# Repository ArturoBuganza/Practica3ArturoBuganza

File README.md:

# Practica3ArturoBuganza
This is the third practice form the microcontoller laboratory

## Objectives

Build the minimum system from the designs that thei student made on the practices 1 and 2.

## Introduction

Microcontrollers are all around  he world. Each day, Microcontrollers, are more present in the many aspects of our lives: in our work, inside our houses, and in more. We can find them controlling small devices like cellphones, microwaves, washing machines, and televisions.

A microcontroller is one device or chip that is used to govern one or more processes. For example, the controller that regulates the room temperature of an air conditioner; it has a sensor that continuously measures the internal temperature and, when the preset limits are exceeded, it generates the necessary signals to adjust the temperature.

## State of the Art

### The practices and the PIC microcontroller

The main objective of this practices is to provide students the foundation to fully understand the operation of the PIC18F45K50 microcontroller. This will be achieved through 11 documents that will guide the reader to create their own electronic card or Printed Circuit Board (PCB) and to be able to program it; in order to, execute different functions.

The advantages of ta PIC microcontroller to others on the market, which is why it will be used throughout this manual, are as follows:

- Easy to operate.
- There is enough documentation to work with it and it’s easy to obtain it.
- The price is comparatively lower than its competitors.
- It has a high operating speed.
- Development tools are cheap and easy to use.
- There are a variety of hardware that can record, erase and check the behavior of PIC.
- Once you learn to handle a PIC, it will easier to handle any other models of microcontrollers.

### KiCad EDA Software

KiCad is an open source software suite for Electronic Design Automation (EDA). The programs handle Schematic Capture,
and PCB Layout with Gerber output. The suite runs on Windows, Linux and macOS and is licensed under GNU GPL v3. The
first release date was in 1992 by its original author, Jean-Pierre Charras, but is now currently under development by
the KiCad Developers Team. 

## Results

This practice is pretty fast, but it makes us look at the final product as a simulation, in order for we to obtain this we needed to export the files to make them ready to be printed or hand crafted into the silicon plate. The results were satisfiying, the screenshots are forward ahead in the Demonstration section.

### Follow the next 'Project Configuration' Steps

1. Now that your PCB is completed, you can generate the Gerber files for each layer of your board. Click on Perform design rules check as shown in Fig. 1. Then click on the Run DCR, if everything goes right you will get no message of error, as show in figure 2.

2. Click on File→Plot... Select ‘Gerber’ as ‘Plot Format,’also you must choose a folder to save your generated files. Make sure that only the next options are selected: B.Cu from ‘Layers’ box, Exclude PCB edge layer from other layers from ‘Options’ box, and Use proper filename extensions from ‘Gerber Options’ box; as shown in Fig. 3.

3. Finally, click on ‘Plot’ and then click on Generate Drill File. A new window will appear with some options on default. In the section Excellon Drill File Options select the ‘PTH and NPTH holes in single file’ box, then click on the button ‘Generate Drill File.’ Next, in the section Drill Map File Format change to ‘PDF’ box and click on ‘Generate Drill File’ again, see Fig. 4.

4. Once the Gerber and Drill files are generated, you can check your track design [here](https://www.pcbgogo.com/GerberViewer.html). Use the file with the .gbl and .drl extension.

### Report
For this practice, modify only the Conclusion section. Commit an push the changes on the fork of this repository and add
upload the link on Canvas.

### File uploads
Commit and push the files with extensions .pro, .gbl, and .drl  created once you completed all the steps of the document in the repository.

### Demonstration
Screenshot drill.

Screenshot gerber.

## Conclusion

This third practice was significantly faster than the last two. This last step allows us to look at the holes needed to drill, and the cupper pats that need to be added in the piece in order for it to work properly.

The gerber view allows us to see the paths and conections, while the drill view helps us with the holes proyection. Combining these two we get a good idea of the possible final product.

The hardest part here was to follow the steps correctly, but it wasnt that hard since it is described in the practice click by click.

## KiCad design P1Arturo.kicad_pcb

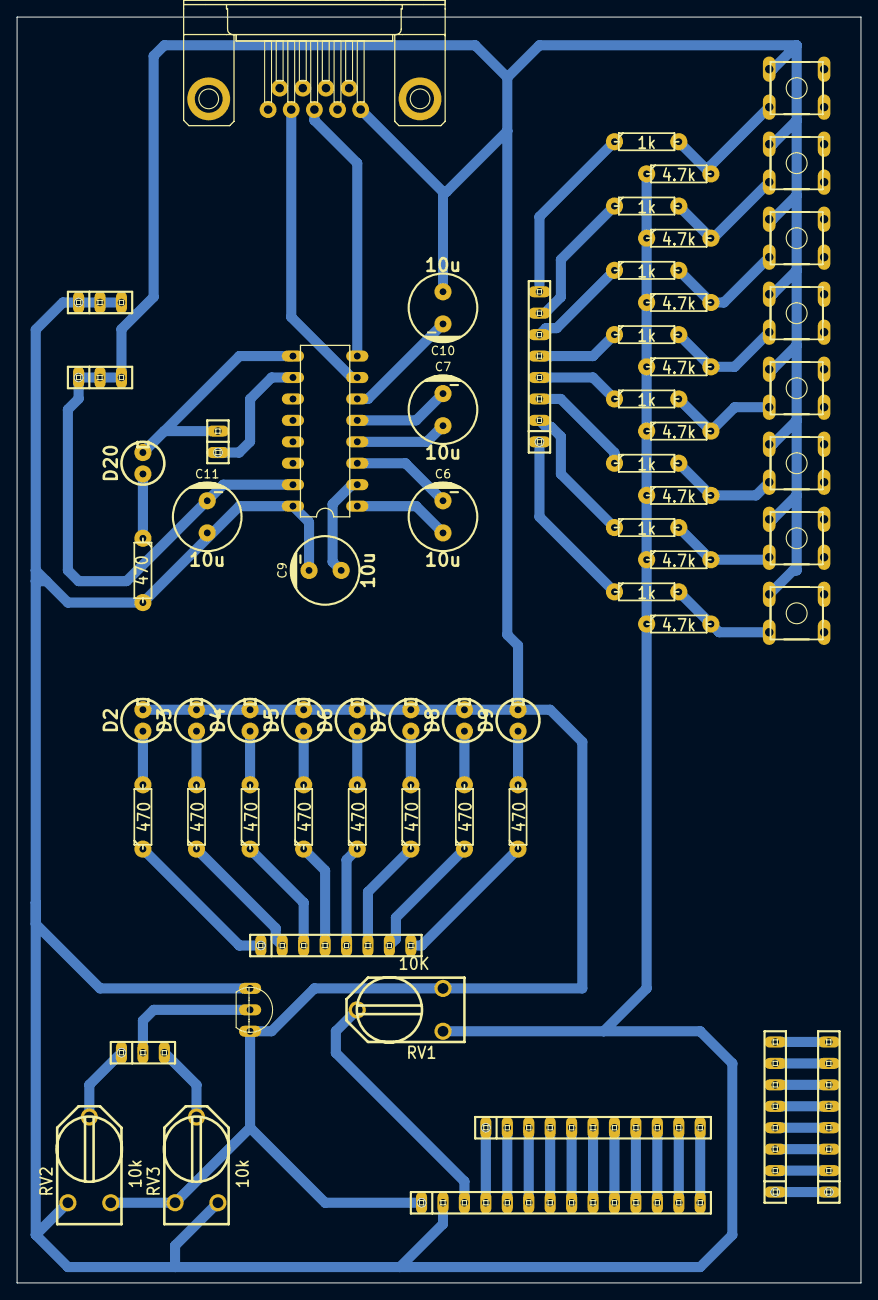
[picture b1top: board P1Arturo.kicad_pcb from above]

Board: 2 copper layers, 100.0 x 150.0 mm, 63 parts (0 on the bottom side), 68 nets.

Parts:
C6, C7, C9, C10, C11: 10u; Capacitor_elec_8x13mm
D2, D3, D4, D5, D6, D7, D8, D9, D20: LED; Led
JP3, JP11, JP23, JP24: PINHD-1X8; pinhead-1X08
JP5: PINHD-1X2; pinhead-1X02
JP9, JP10, JP15: PINHD-1X3; pinhead-1X03
JP13: PINHD-1X11; pinhead-1X11
JP14: PINHD-1X14; pinhead-1X14
R3, R4, R5, R6, R7, R8, R9, R10, R11: 470; Resistor
R12, R13, R14, R15, R16, R17, R18, R19: 1k; Resistor
R20, R21, R22, R23, R24, R25, R26, R27: 4.7k; Resistor
RV1: 10K; RV2X4
RV2, RV3: 10k; RV2X4
S2, S3, S4, S5, S6, S7, S8, S9: DTS-6
U3: MCP9700A
U4: MAX232; Maxim232
X2: F09HP; Conector_F09HP

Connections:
+5VA: C9.2, C11.1, JP9.1, JP9.2, JP9.3, JP14.2, R3.2, R20.1, R21.1, R22.1, R23.1, R24.1, R25.1, R26.1, R27.1, RV1.1, RV2.1, RV3.3, U3.1, U4.16
GNDA: C10.1, C11.2, D2.2, D3.2, D4.2, D5.2, D6.2, D7.2, D8.2, D9.2, JP10.1, JP10.2, JP10.3, JP14.1, RV1.3, RV2.3, RV3.1, S2.1, S3.1, S4.1, S5.1, S6.1, S7.1, S8.1, S9.1, U3.3, U4.15, X2.5
unnamed: C6.1, U4.1
unnamed: C6.2, U4.3
unnamed: C7.1, U4.4
unnamed: C7.2, U4.5
unnamed: C9.1, U4.2
unnamed: C10.2, U4.6
unnamed: D2.1, R11.2
unnamed: D3.1, R10.2
unnamed: D4.1, R9.2
unnamed: D5.1, R8.2
unnamed: D6.1, R7.2
unnamed: D7.1, R6.2
unnamed: D8.1, R5.2
unnamed: D9.1, R4.2
unnamed: D20.1, R3.1
unnamed: D20.2, JP5.2, U4.9
unnamed: JP5.1, U4.10
unnamed: JP11.1, R11.1
unnamed: JP11.2, R10.1
unnamed: JP11.3, R9.1
unnamed: JP11.4, R8.1
unnamed: JP11.5, R7.1
unnamed: JP11.6, R6.1
unnamed: JP11.7, R5.1
unnamed: JP11.8, R4.1
unnamed: JP13.1, JP14.4
unnamed: JP13.2, JP14.5
unnamed: JP13.3, JP14.6
unnamed: JP13.4, JP14.7
unnamed: JP13.5, JP14.8
unnamed: JP13.6, JP14.9
unnamed: JP13.7, JP14.10
unnamed: JP13.8, JP14.11
unnamed: JP13.9, JP14.12
unnamed: JP13.10, JP14.13
unnamed: JP13.11, JP14.14
unnamed: JP14.3, RV1.2
unnamed: JP15.1, RV2.2
unnamed: JP15.2, U3.2
unnamed: JP15.3, RV3.2
unnamed: JP3.1, JP23.1
unnamed: JP3.2, JP23.2
unnamed: JP3.3, JP23.3
unnamed: JP3.4, JP23.4
unnamed: JP3.5, JP23.5
unnamed: JP3.6, JP23.6
unnamed: JP3.7, JP23.7
unnamed: JP3.8, JP23.8
unnamed: JP24.1, R12.1
unnamed: JP24.2, R13.1
unnamed: JP24.3, R14.1
unnamed: JP24.4, R15.1
unnamed: JP24.5, R16.1
unnamed: JP24.6, R17.1
unnamed: JP24.7, R18.1
unnamed: JP24.8, R19.1
unnamed: R12.2, R20.2, S2.3
unnamed: R13.2, R21.2, S3.3
unnamed: R14.2, R22.2, S4.3
unnamed: R15.2, R23.2, S5.3
unnamed: R16.2, R24.2, S6.3
unnamed: R17.2, R25.2, S7.3
unnamed: R18.2, R26.2, S8.3
unnamed: R19.2, R27.2, S9.3
unnamed: U4.7, X2.2
unnamed: U4.8, X2.3
